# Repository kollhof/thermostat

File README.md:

# thermostat
ESP32 based thermostat for a DIY heating system

## gettting started

Create a factory NVS partitions with hardware and homekit config:

```bash
../esp-homekit-sdk/tools/mfg_homekit/hk_mfg_gen.py --conf mfg-config.csv --values mfg-values.csv --prefix thermo --cid 9 --outdir ./secret/mfg/ --size 0x6000
```

Flash factory partitions to individual devices:

```bash
esptool.py write_flash 0x340000 secret/mfg/bin/thermo-[homekit-setup-id].bin
```

Flash firmware:

```bash
idf.py clean build flash
```

Update firmware over the air:

The Device ID can be found as serial number in Homekit once paired.
```bash
idf.py -DOTA_DEVICE_ID=[device-id] clean build flash-ota
```

## progress

This first version used an ESP32-WROVER-V4 powered by a Hi-link power supply all badly soldered to a protboard with way too thick wires.

After reading up on powersupplies I decided to ditch the Hi-link for a Recom RAC03-05SK. It does not need any extra components to be safe which made things a bit simpler.

The female pin headers were awful to work with and I wanted a bit more ports exposed for experimenting.

I also started to get a tiny bit better at soldering, and my choice of wires improved as well.

Now I had a pretty well working little board. I used Dallas ds18b20 sensors to measure temperatur and relays to drive the electric radiators.

I needed about 5 of these boards, wiring and soldering everything got old pretty quickly. Instead of continuing to use protoboards, I decided to design my own PCB. I downloaded KiCad, looked at many ESP-32 dev board schematics for inspiration and created my own little board.

I had them printed by https://aisler.net and few days later I had a 3 PCBs and all the parts needed. I soldered all the SMD components using a hot air blower,and everything just worked!

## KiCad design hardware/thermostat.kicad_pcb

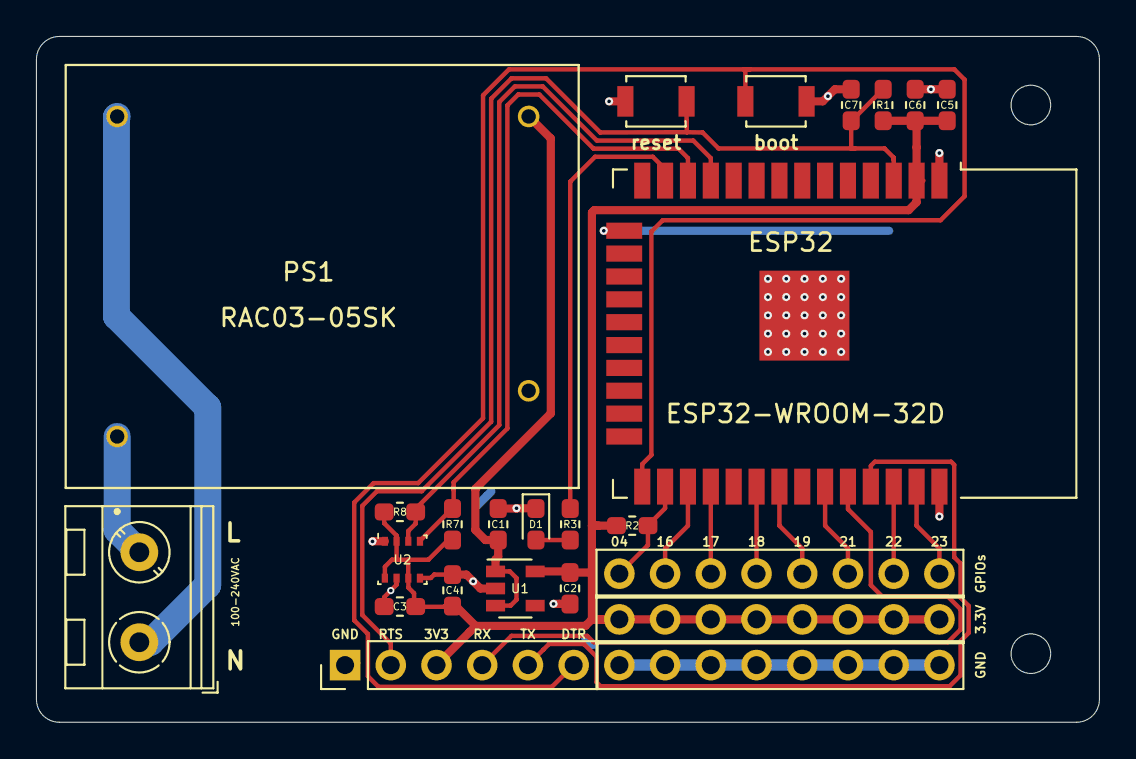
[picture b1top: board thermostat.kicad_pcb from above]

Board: 2 copper layers, 59.1 x 38.1 mm, 27 parts (1 on the bottom side), 21 nets.

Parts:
C1: 1.0uF; C_0603_1608Metric_Pad1.05x0.95mm_HandSolder
C2: 2.2uF; C_0603_1608Metric_Pad1.05x0.95mm_HandSolder
C3, C4, C6, C7: 0.1uF; C_0603_1608Metric_Pad1.05x0.95mm_HandSolder
C5: 22uF; C_0603_1608Metric_Pad1.05x0.95mm_HandSolder
D1: status; LED_0603_1608Metric_Pad1.05x0.95mm_HandSolder
ESP32: ESP32-WROOM-32D; ESP32-WROOM-32
H1, H2: MountingHole; MountingHole_2.2mm_M2_ISO7380
J1: 230AC; TerminalBlock_RND_205-00045_1x02_P5.00mm_Horizontal
J2: program; PinHeader_1x06_P2.54mm_Vertical
J3: 3.3V; PinHeader_1x08_P2.54mm_Vertical
J4: GND; PinHeader_1x08_P2.54mm_Vertical
J5: GPIOs; PinHeader_1x08_P2.54mm_Vertical
LOGO1: Logo_Open_Hardware_Small; OSHW-Symbol_6.7x6mm_SilkScreen
PS1: RAC03-05SK; CONV_RAC03-05SK
R1: 10K; R_0603_1608Metric_Pad1.05x0.95mm_HandSolder
R2, R7, R8: 4.7k; R_0603_1608Metric_Pad1.05x0.95mm_HandSolder
R3: 1k; R_0603_1608Metric_Pad1.05x0.95mm_HandSolder
SW1: reset; SW_SPST_B3U-1000P
SW2: boot; SW_SPST_B3U-1000P
U1: AP2112K-3.3; SOT-23-5
U2: BME280; Bosch_LGA-8_2.5x2.5mm_P0.65mm_ClockwisePinNumbering

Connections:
+3V3: C2.1, C3.1, C4.1, C5.1, C6.1, ESP32.2, J2.3, J3.1, J3.2, J3.3, J3.4, J3.5, J3.6, J3.7, J3.8, R1.1, R2.1, R7.1, R8.1, U1.5, U2.2, U2.6, U2.8
+5V: C1.1, PS1.3, U1.1, U1.3
/L: J1.2, PS1.1
/N: J1.1, PS1.4
EN: C7.2, ESP32.3, J2.2, R1.2, SW1.2
GND: C1.2, C2.2, C3.2, C4.2, C5.2, C6.2, C7.1, D1.1, ESP32.1, ESP32.15, ESP32.38, ESP32.39, J2.1, J4.1, J4.2, J4.3, J4.4, J4.5, J4.6, J4.7, J4.8, PS1.2, SW1.1, SW2.1, U1.2, U2.1, U2.5, U2.7
IO4: ESP32.26, J5.1, R2.2
IO14: ESP32.13, R3.1
IO16: ESP32.27, J5.2
IO17: ESP32.28, J5.3
IO18: ESP32.30, J5.4
IO19: ESP32.31, J5.5
IO21: ESP32.33, J5.6
IO22: ESP32.36, J5.7
IO23: ESP32.37, J5.8
IO26: ESP32.11, R8.2, U2.3
IO27: ESP32.12, R7.2, U2.4
unnamed: D1.2, R3.2
RX: ESP32.34, J2.4
TX: ESP32.35, J2.5
boot: ESP32.25, J2.6, SW2.2

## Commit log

2020-01-05 initial thermostat code
2020-01-06 adding board config and stats reporting
2020-01-19 update stats
2020-01-19 retry connecting forever, include version in stats
2020-01-19 correct board ID
2020-01-19 reconnect forever
2020-01-24 add KiCad files for custom PCBs
2020-01-25 remove unused code
2020-01-29 add new board
2020-02-01 trying out modulation of power to heating vs on off
2020-02-15 changing task priorities, setting min temp
2020-03-31 persist target temp
2020-12-02 fix temp threshhold, allow config of duty cycle length for using short cycles with SSRs
2020-12-08 feat(led): dim LED based on heating state
2020-12-20 add native support for homekit, simplify firmware upgrade by using a factory partition with board configs, add support for unified provisioning
2020-12-20 add pics
2020-12-20 fix readme
2021-01-01 cleanup
2021-01-08 add support for BLE temp sensors
2021-11-21 add support for signaling ow battary fault when BLE temp sensor cannot be read
2022-12-08 remove wired temp sensor, add watchdog for BLE sensor
2023-02-17 feat: add humidity and improve hostname

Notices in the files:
hardware/thermostat.kicad_pcb:
protoboard V0.7 (CC BY-SA 4.0)
